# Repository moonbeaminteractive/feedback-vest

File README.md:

# feedback-vest
vest with haptic and visual feedback

## Circuit Diagram - main board

## PCB - main board

## Circuit Diagram - led Ring

## Circuit Diagram - led ring PCB

## circuit diagram and PCB - IR sensors

## Prototype Design

## Hardware
* nRF24L01 Wireless Transceiver
* Arduino Pro Mini
* 1838 Infrared Receiver at 38K HZ Modulation ( *4)
* Dotstar (in ring shape)
* Microphone (*1)
* Vibrator (*2)
* Speaker / buzzer
* ADC (*1)
* Battery

## Communication

https://docs.google.com/spreadsheets/d/1SZP6osHujqh5WhPNwRo56sCZVwubzTMAS0mKgGUERew/edit#gid=0

## Log
### Nov/19/2016

#### Progress
* Tested Arduino Pro Mini with blink example
* Tested IR receiver with IR led, as well as TV remote controller
* Tested nRF24L01 wireless transceiver

#### Difficulties
* IR emitter is much lower than expected [suggestion from Matt: use an NPN (bjt or mosfet) transistor to supply more current]
* Order ring shape dotstar

#### Next Steps
* Test communication between multiple nRF24L01 wireless transceiver
* Check communication protocol between arm, weapon and pickup group
* Design iteration: meeting with other groups about the size of different components
* Notification system design with Buzzer/microphone and dotstar

### Nov/21/2016
#### Progress
* Tested communication between two nRF24L01 wireless transceivers, send & receive signal successfully

# Vest-to-Weapons Connection

Table of Vest-to-Weapon connections

| Pin | Signal |
| --- | --- |
| 1 | V50 |
| 2 | TX(Vest), RX(Weapon) |
| 3 | RX(Vest), TX(Weapon) |
| 4 | GND |

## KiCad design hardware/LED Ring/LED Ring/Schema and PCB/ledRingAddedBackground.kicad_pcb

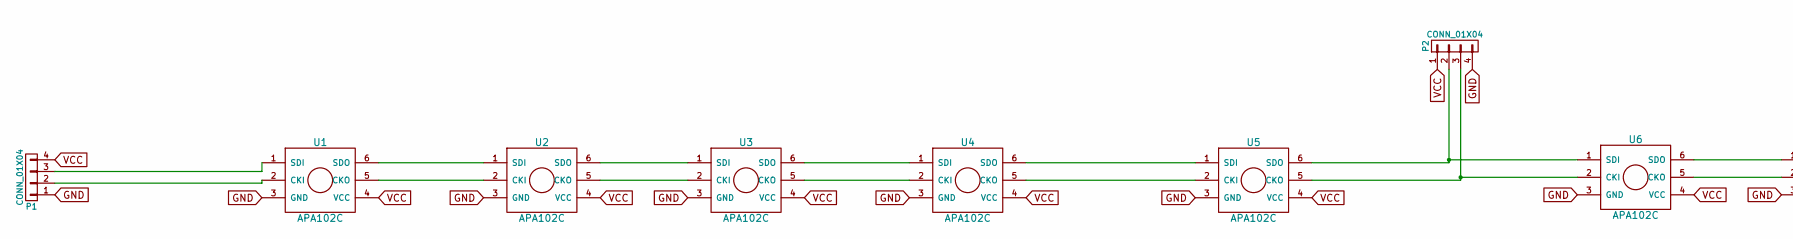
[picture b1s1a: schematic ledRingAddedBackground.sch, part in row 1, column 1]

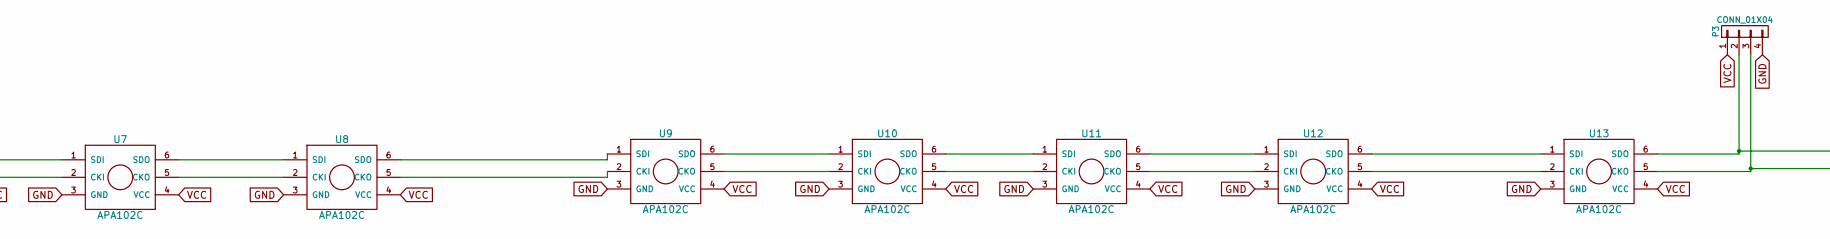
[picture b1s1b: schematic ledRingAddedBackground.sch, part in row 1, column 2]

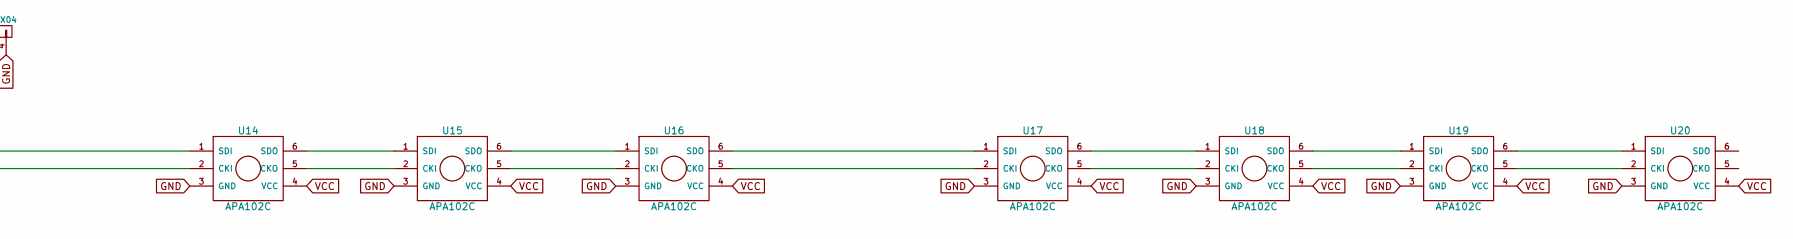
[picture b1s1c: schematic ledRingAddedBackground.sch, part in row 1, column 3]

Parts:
P1, P2, P3: CONN_01X04; Pin_Header_Straight_1x04
U1, U2, U3, U4, U5, U6, U7, U8, U9, U10, U11, U12, U13, U14, U15, U16, U17, U18, U19, U20: APA102C; APA102C-80

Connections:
GND: P1.1, P2.4, P3.4, U1.3 (GND), U2.3 (GND), U3.3 (GND), U4.3 (GND), U5.3 (GND), U6.3 (GND), U7.3 (GND), U8.3 (GND), U9.3 (GND), U10.3 (GND), U11.3 (GND), U12.3 (GND), U13.3 (GND), U14.3 (GND), U15.3 (GND), U16.3 (GND), U17.3 (GND), U18.3 (GND), U19.3 (GND), U20.3 (GND)
unnamed: P1.2, U1.2 (CKI)
unnamed: P1.3, U1.1 (SDI)
unnamed: P2.2, U5.6 (SDO), U6.1 (SDI)
unnamed: P2.3, U5.5 (CKO), U6.2 (CKI)
unnamed: P3.2, U13.6 (SDO), U14.1 (SDI)
unnamed: P3.3, U13.5 (CKO), U14.2 (CKI)
unnamed: U1.5 (CKO), U2.2 (CKI)
unnamed: U1.6 (SDO), U2.1 (SDI)
unnamed: U2.5 (CKO), U3.2 (CKI)
unnamed: U2.6 (SDO), U3.1 (SDI)
unnamed: U3.5 (CKO), U4.2 (CKI)
unnamed: U3.6 (SDO), U4.1 (SDI)
unnamed: U4.5 (CKO), U5.2 (CKI)
unnamed: U4.6 (SDO), U5.1 (SDI)
unnamed: U6.5 (CKO), U7.2 (CKI)
unnamed: U6.6 (SDO), U7.1 (SDI)
unnamed: U7.5 (CKO), U8.2 (CKI)
unnamed: U7.6 (SDO), U8.1 (SDI)
unnamed: U8.5 (CKO), U9.2 (CKI)
unnamed: U8.6 (SDO), U9.1 (SDI)
unnamed: U9.6 (SDO), U10.1 (SDI)
unnamed: U9.5 (CKO), U10.2 (CKI)
unnamed: U10.5 (CKO), U11.2 (CKI)
unnamed: U10.6 (SDO), U11.1 (SDI)
unnamed: U11.5 (CKO), U12.2 (CKI)
unnamed: U11.6 (SDO), U12.1 (SDI)
unnamed: U12.5 (CKO), U13.2 (CKI)
unnamed: U12.6 (SDO), U13.1 (SDI)
unnamed: U14.5 (CKO), U15.2 (CKI)
unnamed: U14.6 (SDO), U15.1 (SDI)
unnamed: U15.5 (CKO), U16.2 (CKI)
unnamed: U15.6 (SDO), U16.1 (SDI)
unnamed: U16.5 (CKO), U17.2 (CKI)
unnamed: U16.6 (SDO), U17.1 (SDI)
unnamed: U17.5 (CKO), U18.2 (CKI)
unnamed: U17.6 (SDO), U18.1 (SDI)
unnamed: U18.5 (CKO), U19.2 (CKI)
unnamed: U18.6 (SDO), U19.1 (SDI)
unnamed: U19.5 (CKO), U20.2 (CKI)
unnamed: U19.6 (SDO), U20.1 (SDI)
VCC: P1.4, P2.1, P3.1, U1.4 (VCC), U2.4 (VCC), U3.4 (VCC), U4.4 (VCC), U5.4 (VCC), U6.4 (VCC), U7.4 (VCC), U8.4 (VCC), U9.4 (VCC), U10.4 (VCC), U11.4 (VCC), U12.4 (VCC), U13.4 (VCC), U14.4 (VCC), U15.4 (VCC), U16.4 (VCC), U17.4 (VCC), U18.4 (VCC), U19.4 (VCC), U20.4 (VCC)

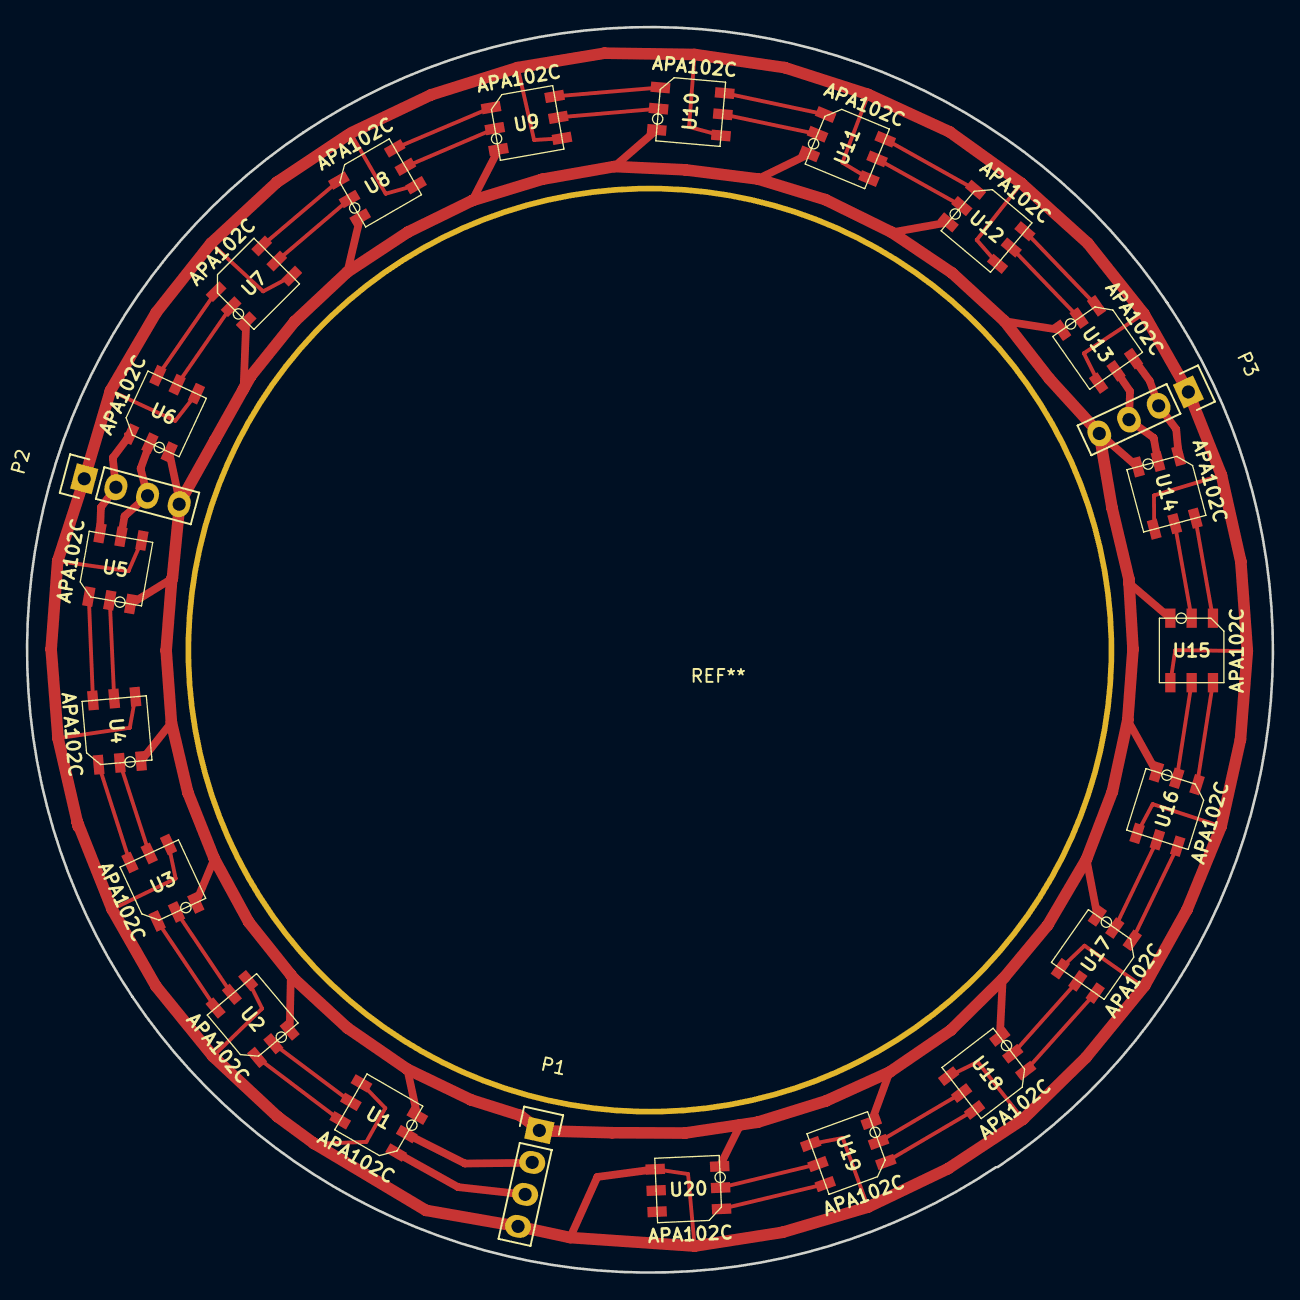
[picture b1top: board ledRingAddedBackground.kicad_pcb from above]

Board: 2 copper layers, 96.6 x 96.6 mm, 23 parts (0 on the bottom side), 42 nets.

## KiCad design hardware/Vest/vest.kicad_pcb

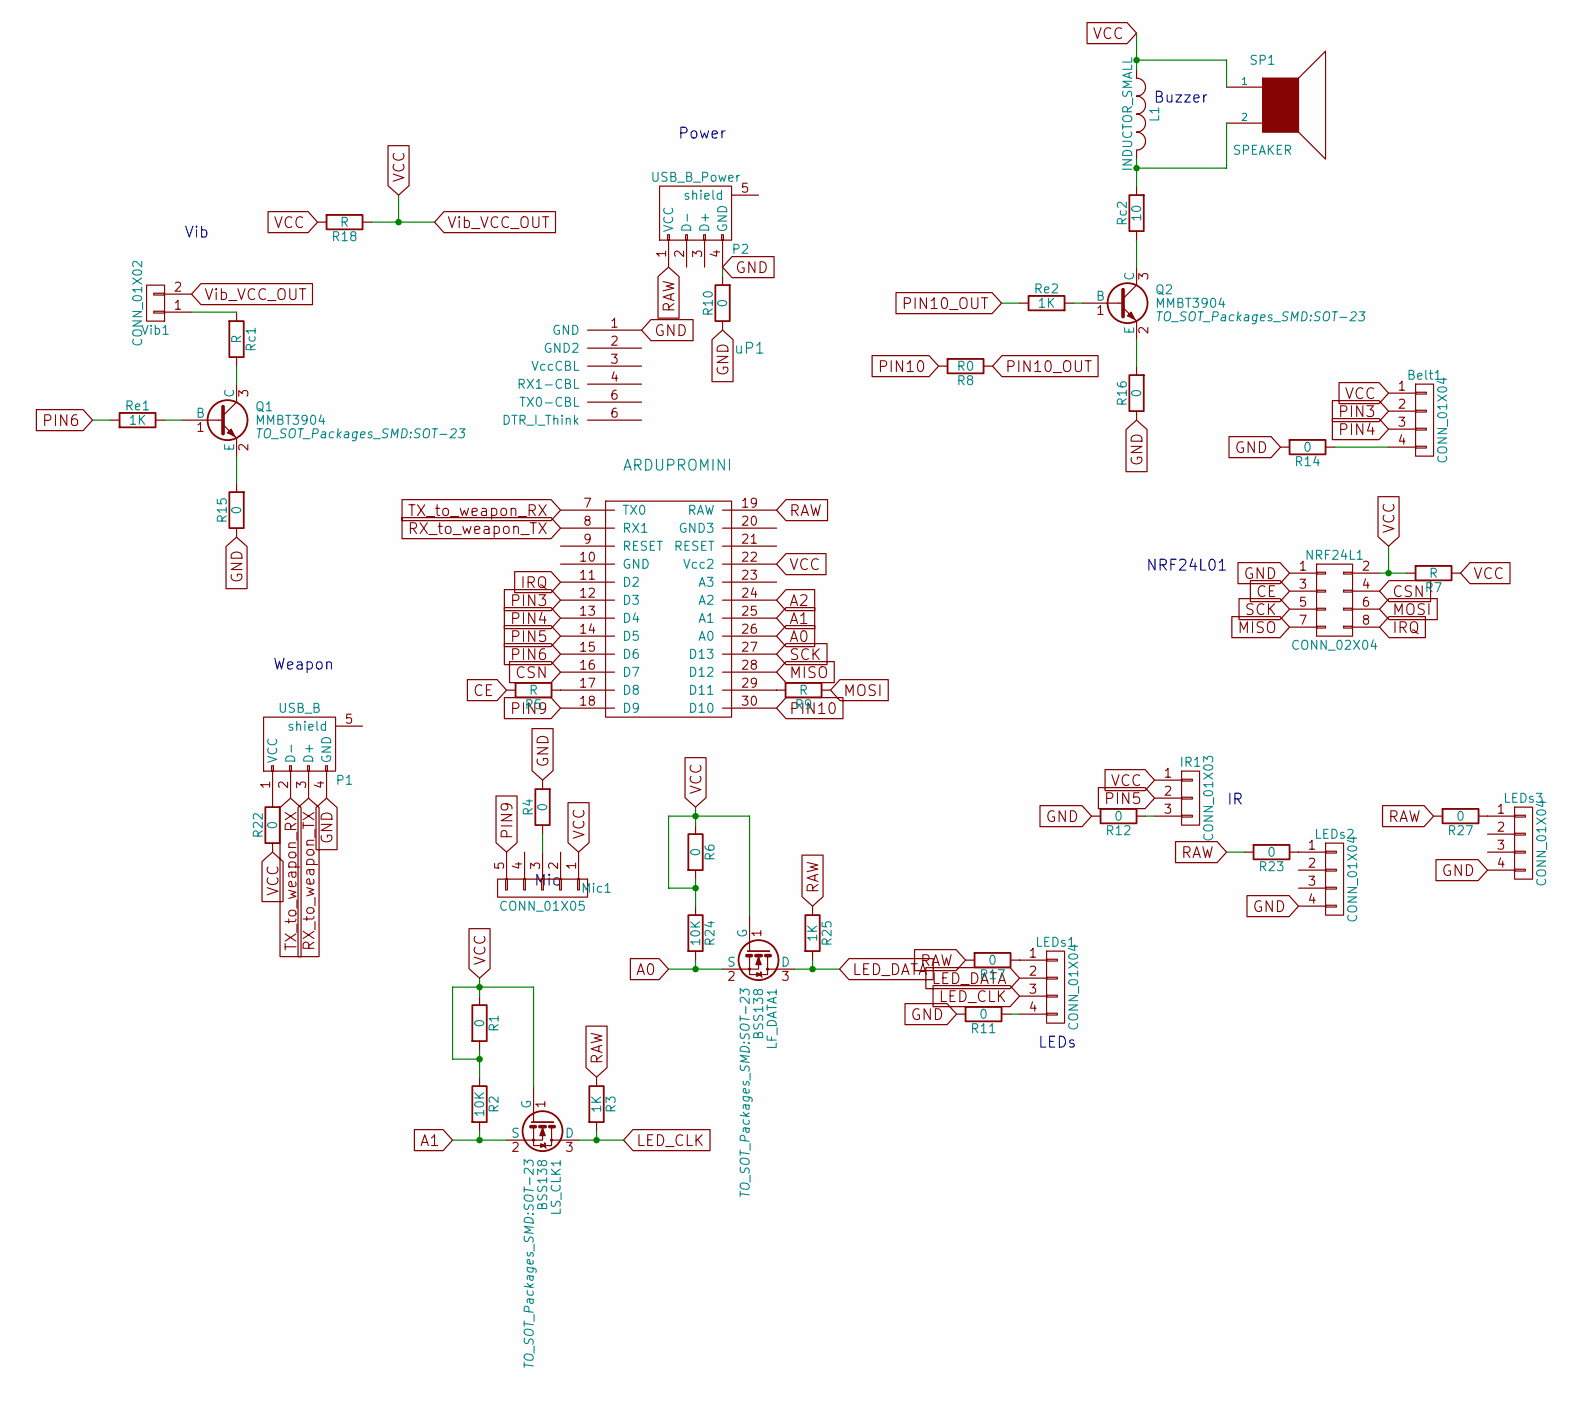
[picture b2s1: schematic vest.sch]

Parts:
Belt1: CONN_01X04; Pin_Header_Straight_1x04
IR1: CONN_01X03; Pin_Header_Straight_1x03
L1: INDUCTOR_SMALL
LEDs1, LEDs2, LEDs3: CONN_01X04; Pin_Header_Straight_1x04
LF_DATA1: BSS138; SOT-23
LS_CLK1: BSS138; SOT-23
Mic1: CONN_01X05; Pin_Header_Straight_1x05
NRF24L1: CONN_02X04; Pin_Header_Straight_2x04
P1: USB_B; USB_A
P2: USB_B_Power; USB_B
Q1, Q2: MMBT3904; SOT-23
R1, R4, R6, R10, R11, R12, R14, R15, R16, R17, R22, R23, R27: 0; R_1206
R2, R24: 10K; R_1206
R3, R25: 1K; R_1206
R5, R9: R; R_1206
R7, R18: R; R_2010
R8: R0; R_2512
Rc1: R; R_1206
Rc2: 10; R_1206
Re1, Re2: 1K; R_1206
SP1: SPEAKER; MagneticBuzzer_ProSignal_ABI-010-RC
Vib1: CONN_01X02; Pin_Header_Straight_1x02
uP1: ARDUPROMINI; ArduProMini

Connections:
A0: LF_DATA1.2 (S), R24.2, uP1.26 (A0)
A1: LS_CLK1.2 (S), R2.2, uP1.25 (A1)
A2: uP1.24 (A2)
CE: NRF24L1.3, R5.2
CSN: NRF24L1.4, uP1.16 (D7)
GND: LEDs2.4, LEDs3.4, NRF24L1.1, P1.4 (GND), P2.4 (GND), R4.2, R10.1, R10.2, R11.2, R12.2, R14.2, R15.1, R16.1, uP1.1 (GND)
IRQ: NRF24L1.8, uP1.11 (D2)
LED_CLK: LEDs1.3, LS_CLK1.3 (D), R3.2
LED_DATA: LEDs1.2, LF_DATA1.3 (D), R25.2
MISO: NRF24L1.7, uP1.28 (D12)
MOSI: NRF24L1.6, R9.1
unnamed: Belt1.4, R14.1
unnamed: IR1.3, R12.1
unnamed: L1.2, Rc2.2, SP1.2
unnamed: LEDs1.1, R17.1
unnamed: LEDs1.4, R11.1
unnamed: LEDs2.1, R23.1
unnamed: LEDs3.1, R27.1
unnamed: Mic1.3, R4.1
unnamed: P1.1 (VCC), R22.2
unnamed: Q1.1 (B), Re1.1
unnamed: Q1.2 (E), R15.2
unnamed: Q1.3 (C), Rc1.1
unnamed: Q2.1 (B), Re2.2
unnamed: Q2.2 (E), R16.2
unnamed: Q2.3 (C), Rc2.1
unnamed: R5.1, uP1.17 (D8)
unnamed: R9.2, uP1.29 (D11)
unnamed: Rc1.2, Vib1.1
PIN3: Belt1.2, uP1.12 (D3)
PIN4: Belt1.3, uP1.13 (D4)
PIN5: IR1.2, uP1.14 (D5)
PIN6: Re1.2, uP1.15 (D6)
PIN9: Mic1.5, uP1.18 (D9)
PIN10: R8.2, uP1.30 (D10)
PIN10_OUT: R8.1, Re2.1
RAW: P2.1 (VCC), R3.1, R17.2, R23.2, R25.1, R27.2, uP1.19 (RAW)
RX_to_weapon_TX: P1.3 (D+), uP1.8 (RX1)
SCK: NRF24L1.5, uP1.27 (D13)
TX_to_weapon_RX: P1.2 (D-), uP1.7 (TX0)
VCC: Belt1.1, IR1.1, L1.1, LF_DATA1.1 (G), LS_CLK1.1 (G), Mic1.1, NRF24L1.2, R1.1, R1.2, R2.1, R6.1, R6.2, R7.1, R7.2, R18.1, R18.2, R22.1, R24.1, SP1.1, Vib1.2, uP1.22 (Vcc2)

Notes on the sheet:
Buzzer
Vib
Mic
LEDs
NRF24L01
Power
Weapon

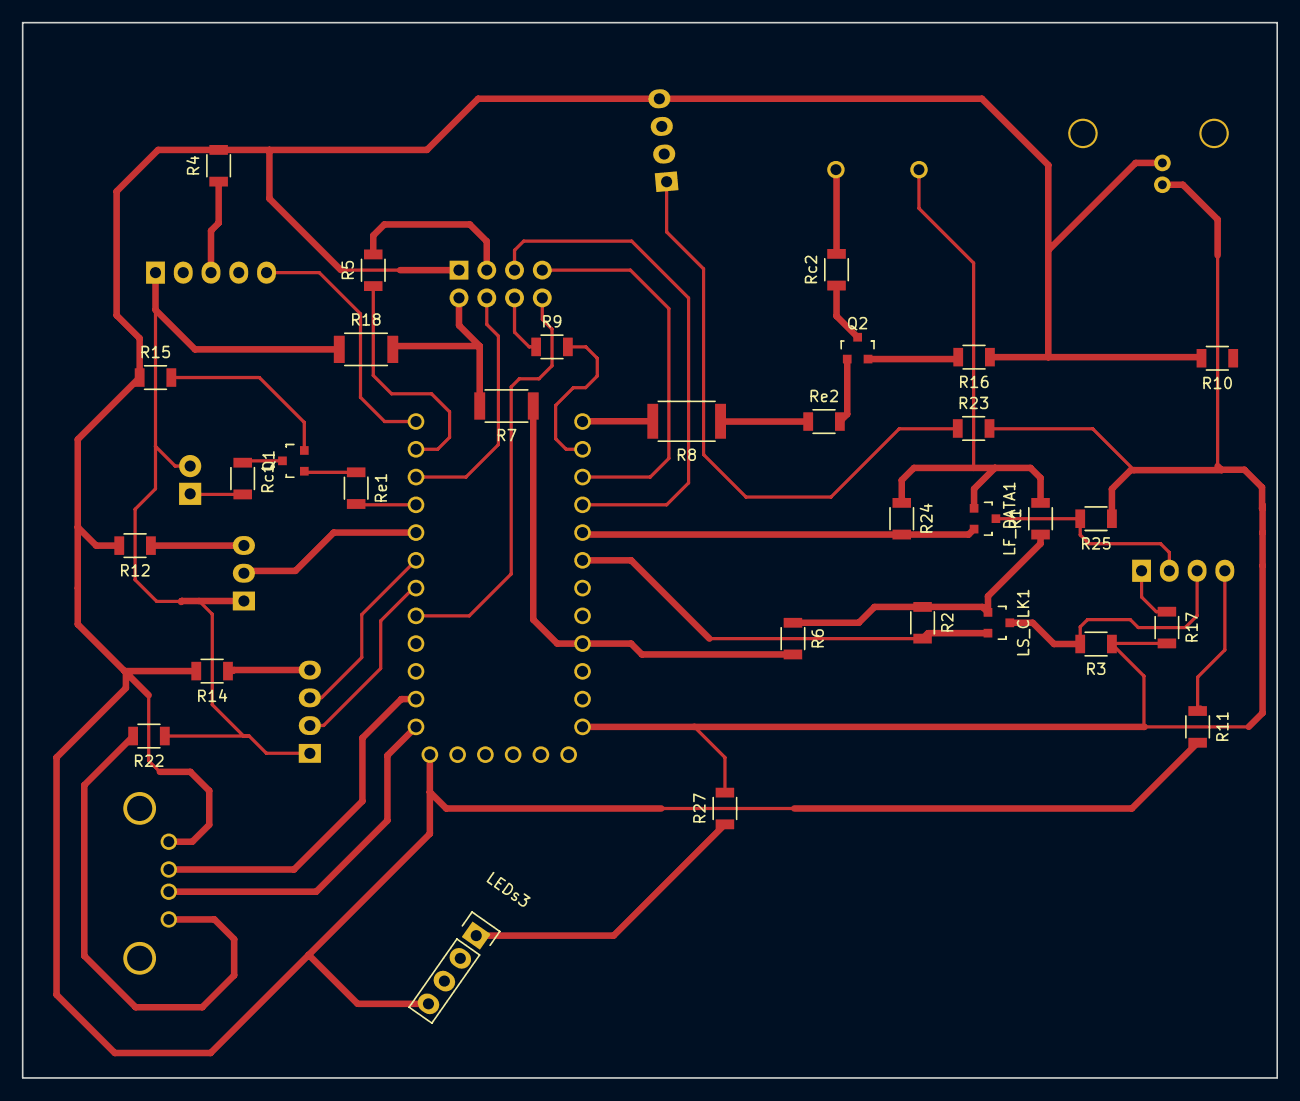
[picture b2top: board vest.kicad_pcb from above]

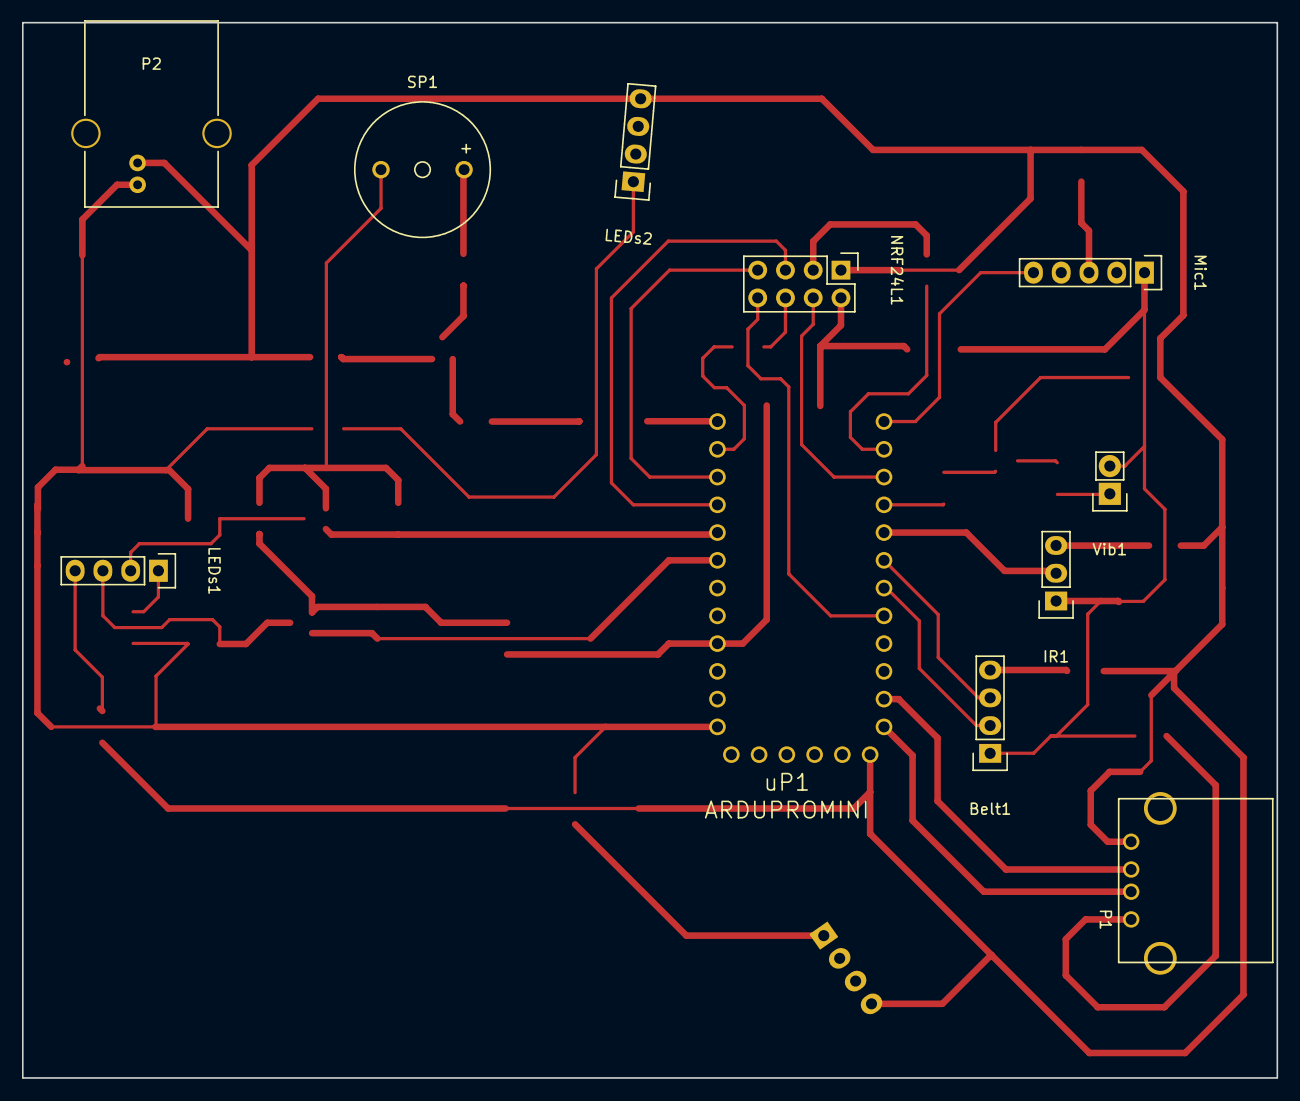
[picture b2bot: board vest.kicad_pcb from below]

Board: 2 copper layers, 114.8 x 96.6 mm, 42 parts (11 on the bottom side), 40 nets.

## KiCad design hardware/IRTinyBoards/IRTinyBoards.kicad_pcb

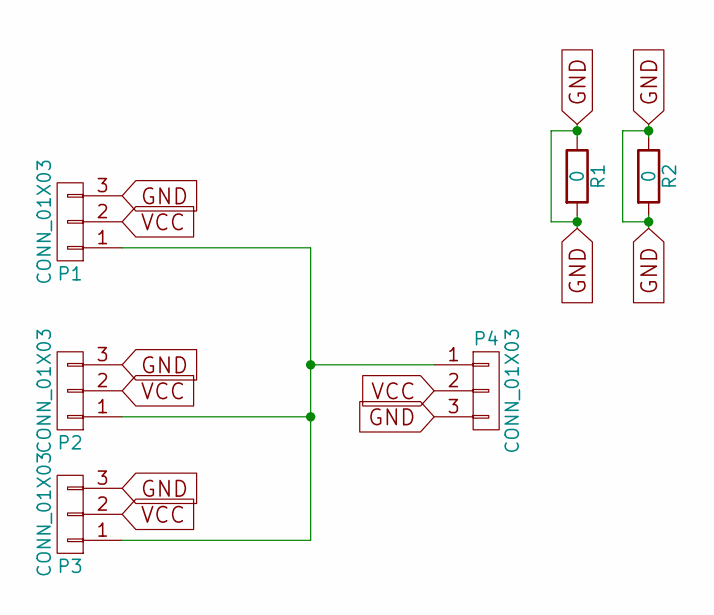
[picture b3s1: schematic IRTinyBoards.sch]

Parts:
P1, P2, P3, P4: CONN_01X03; Pin_Header_Straight_1x03
R1, R2: 0; R_1206

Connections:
GND: P1.3, P2.3, P3.3, P4.3, R1.1, R1.2, R2.1, R2.2
unnamed: P1.1, P2.1, P3.1, P4.1
VCC: P1.2, P2.2, P3.2, P4.2

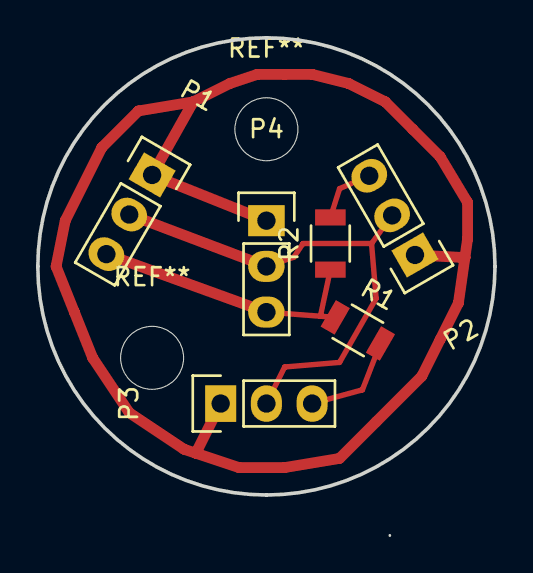
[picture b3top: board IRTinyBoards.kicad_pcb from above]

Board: 2 copper layers, 25.4 x 27.7 mm, 6 parts (0 on the bottom side), 3 nets.

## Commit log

2016-11-13 added folders
2016-11-13 replaced gitignore with empty txt
2016-11-19 Added mockups
2016-11-19 added back.jpg
2016-11-19 Added front.jpg
2016-11-19 Added a picture of testing the IR sensor
2016-12-12 Added pcb design
2016-12-12 Added pcb and circuit diagram
2016-12-13 Updated pcb
2016-12-13 changed transistor from 2222 to MMBT3904
2016-12-13 Updated diagrams
2016-12-13 updated pcb: change track passing through 1206 from 0.6 to 0.3
2016-12-13 Added 2 more connectors
2016-12-13 modified irtinyboards to be at 120 degrees on a circular board
2016-12-14 Updated the entire folder
2016-12-14 minor changes to the vest schematic
2016-12-14 Morse_enDecoder library.
2016-12-14 Vest communication.
2016-12-14 Serial communication with weapon.
2016-12-15 updated image
2016-12-17 Create led ring
2016-12-17 Add files via upload
    LED Ring - Schema and PCB files
2016-12-17 Create images
2016-12-17 vest images
    vest images
2016-12-17 led Ring circuit diagram and pcb Updated
2016-12-17 led ring circuit diagram and pcb
2016-12-17 IR sensors circuit diagram and pcb updated
2016-12-17 physical prototype updated
